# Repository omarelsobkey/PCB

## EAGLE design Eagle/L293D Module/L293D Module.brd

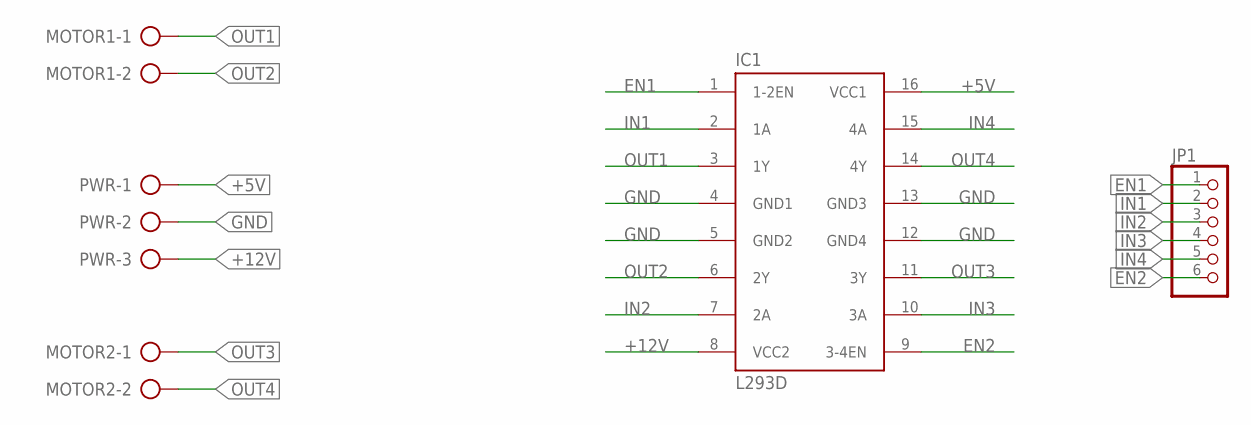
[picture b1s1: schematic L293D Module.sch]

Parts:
IC1: L293D; DIL16
JP1: PINHD-1X6; 1X06
MOTOR1, MOTOR2: AK500/2-H
PWR: AK500/3-H

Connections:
+5V: IC1.16 (VCC1), PWR.1
+12V: IC1.8 (VCC2), PWR.3
EN1: IC1.1 (1-2EN), JP1.1
EN2: IC1.9 (3-4EN), JP1.6
GND: IC1.4 (GND1), IC1.5 (GND2), IC1.12 (GND4), IC1.13 (GND3), PWR.2
IN1: IC1.2 (1A), JP1.2
IN2: IC1.7 (2A), JP1.3
IN3: IC1.10 (3A), JP1.4
IN4: IC1.15 (4A), JP1.5
OUT1: IC1.3 (1Y), MOTOR1.1
OUT2: IC1.6 (2Y), MOTOR1.2
OUT3: IC1.11 (3Y), MOTOR2.1
OUT4: IC1.14 (4Y), MOTOR2.2

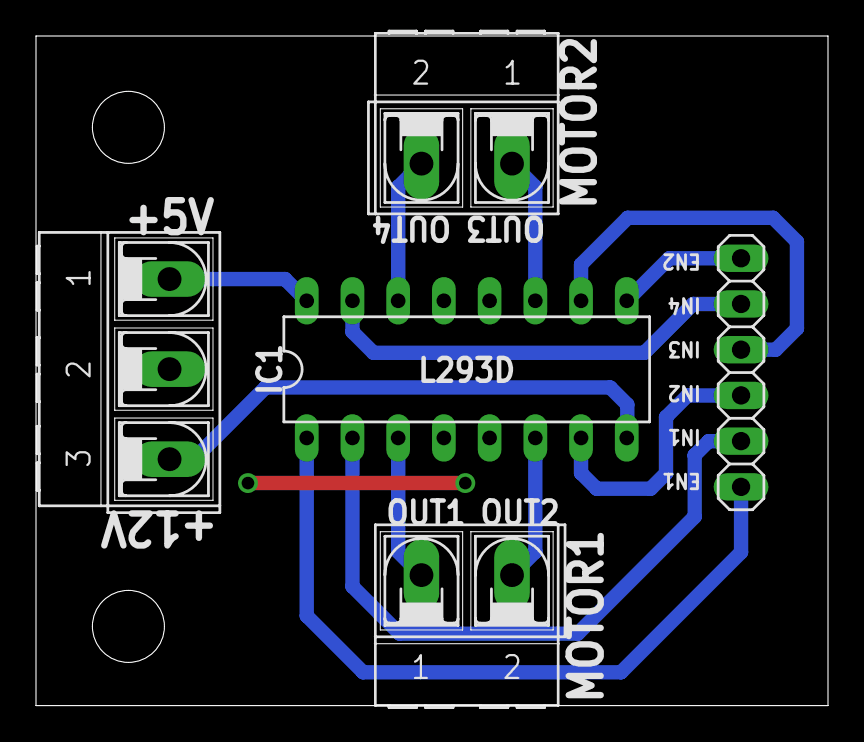
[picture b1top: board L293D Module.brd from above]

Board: 2 copper layers, 44.0 x 37.2 mm, 5 parts (0 on the bottom side), 13 nets.

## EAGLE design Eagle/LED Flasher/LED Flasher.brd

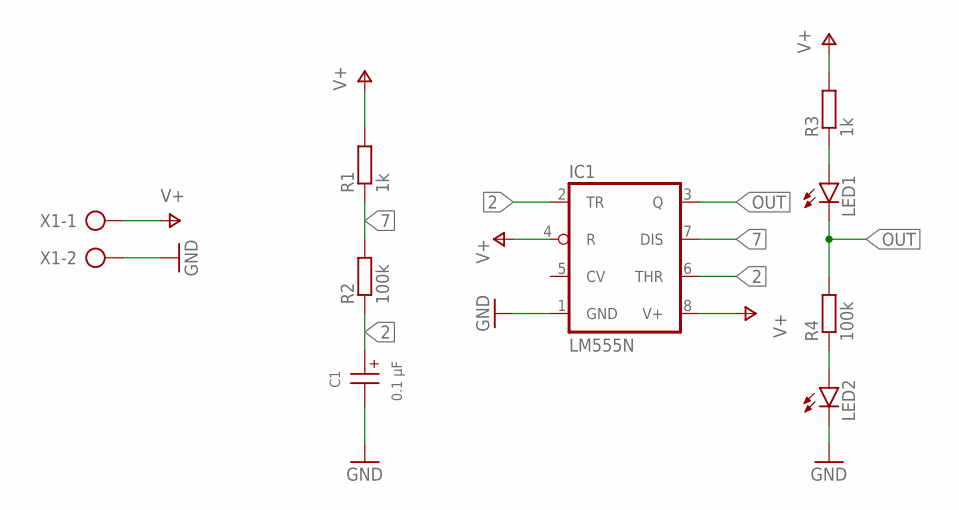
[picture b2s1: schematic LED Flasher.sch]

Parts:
C1: 0.1 µF; WCAP-ATG8_5X11(DXL)
IC1: LM555N; DIL08
LED1, LED2: LED3MM
R1, R3: 1k; 0204/7
R2, R4: 100k; 0204/7
X1: AK300/2

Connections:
2: C1.1 (+), IC1.2 (TR), IC1.6 (THR), R2.1
7: IC1.7 (DIS), R1.1, R2.2
GND: C1.2 (-), IC1.1 (GND), LED2.K (C), X1.2
unnamed: LED1.A, R3.1
unnamed: LED2.A, R4.1
OUT: IC1.3 (Q), LED1.K (C), R4.2
V+: IC1.4 (R), IC1.8 (V+), R1.2, R3.2, X1.1

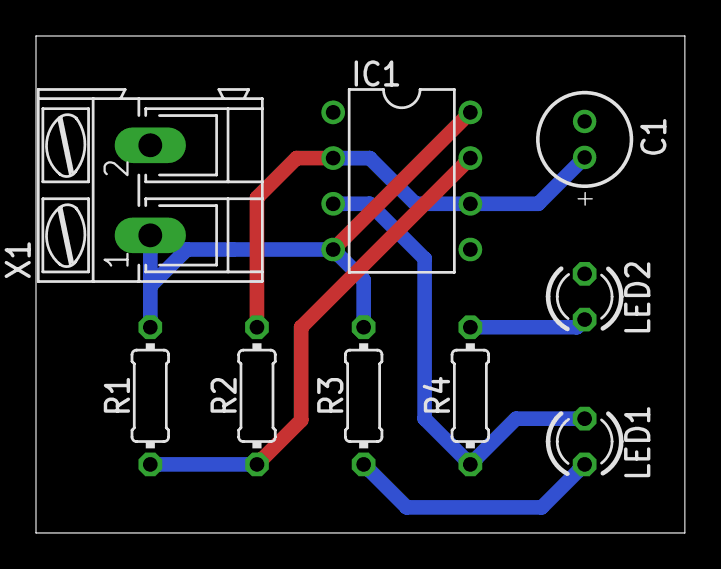
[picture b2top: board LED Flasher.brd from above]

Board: 2 copper layers, 36.0 x 27.6 mm, 9 parts (0 on the bottom side), 7 nets.

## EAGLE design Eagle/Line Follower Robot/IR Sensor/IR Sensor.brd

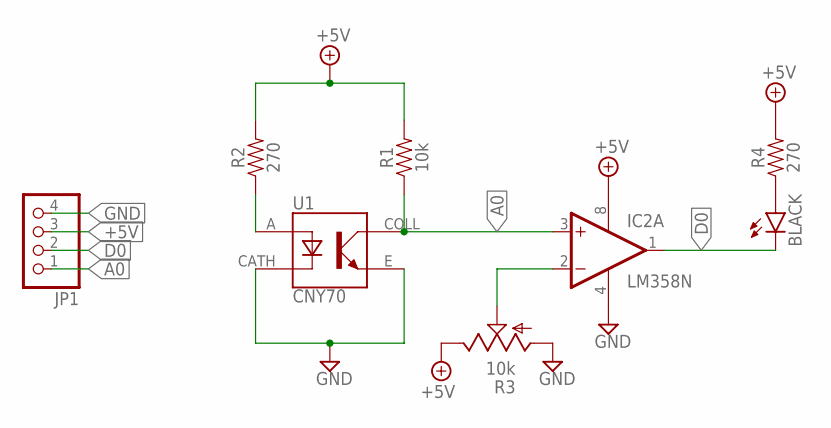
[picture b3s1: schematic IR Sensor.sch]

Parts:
BLACK: LED3MM
IC2: LM358N; DIL08
JP1: PINHD-1X4/90; 1X04/90
R1: 10k; AXIAL-0.3
R2, R4: 270; AXIAL-0.3
R3: 10k; CA6V
U1: CNY70; DIPS254W50P254L710H600Q4

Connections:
+5V: IC2.8 (V+), JP1.3, R1.P$2 (2), R2.P$2 (2), R3.E, R4.P$2 (2)
A0: IC2.3 (+IN), JP1.1, R1.P$1 (1), U1.COLL
D0: BLACK.K (C), IC2.1 (OUT), JP1.2
GND: IC2.4 (V-), JP1.4, R3.A, U1.CATH, U1.E
unnamed: R2.P$1 (1), U1.A
unnamed: IC2.2 (-IN), R3.S
unnamed: BLACK.A, R4.P$1 (1)

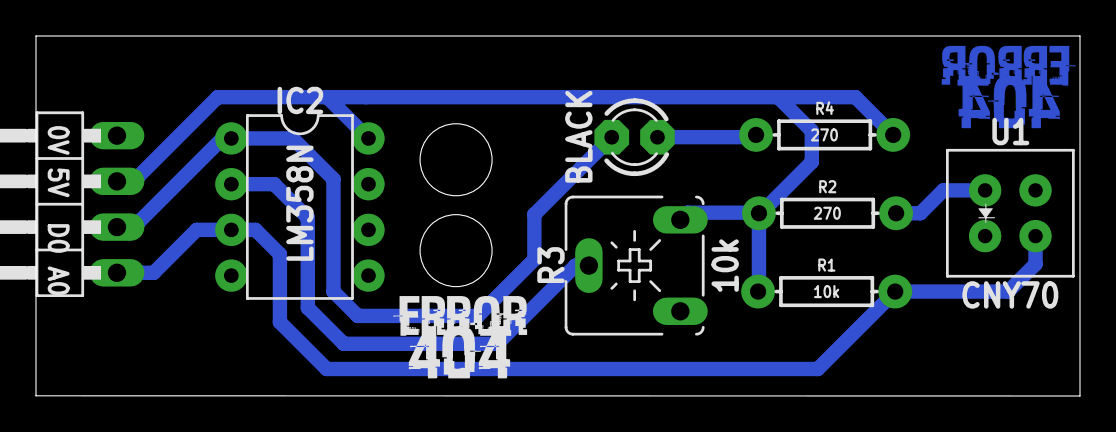
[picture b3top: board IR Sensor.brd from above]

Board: 2 copper layers, 58.0 x 20.0 mm, 10 parts (1 on the bottom side), 7 nets.

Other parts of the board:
U$1: ERROR404_X0.5_T
U$2: ERROR404_X0.5_TN

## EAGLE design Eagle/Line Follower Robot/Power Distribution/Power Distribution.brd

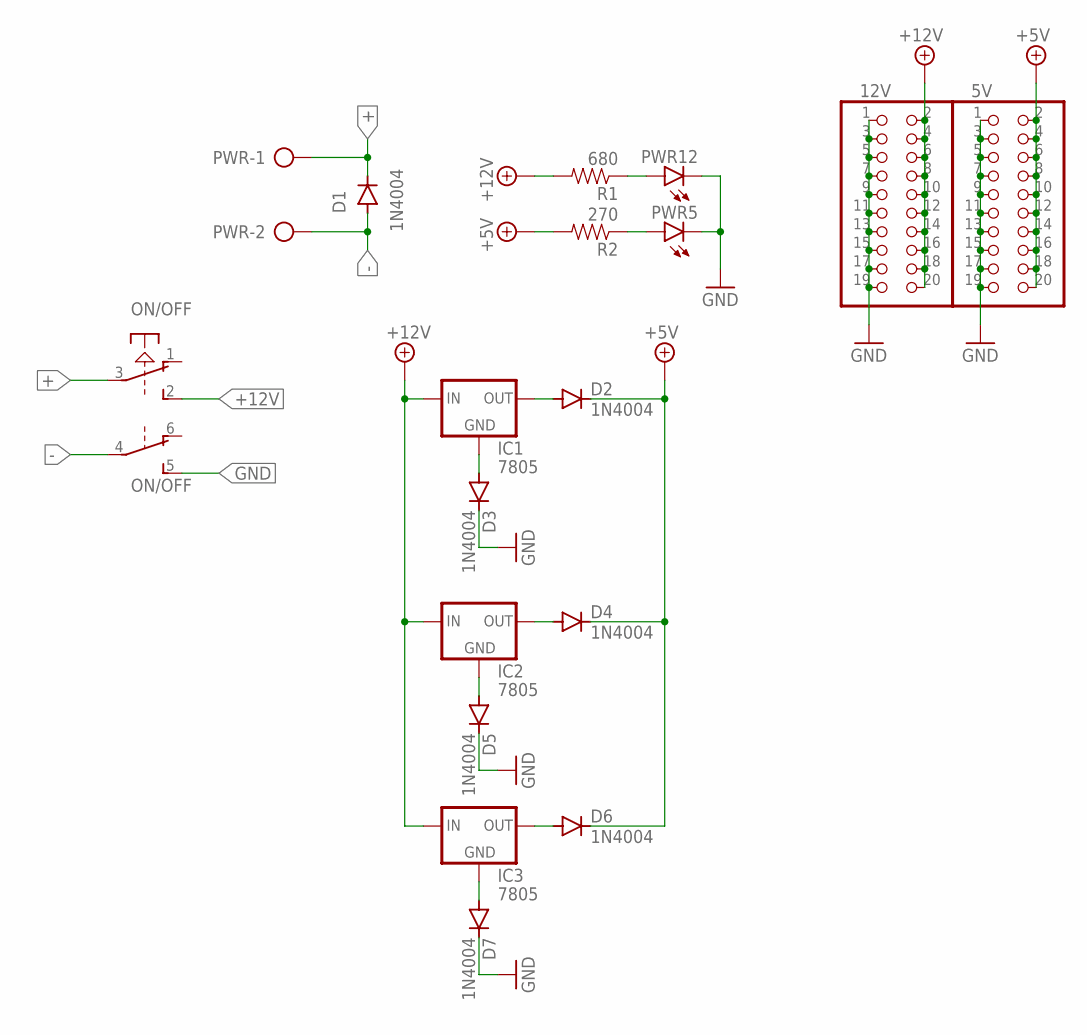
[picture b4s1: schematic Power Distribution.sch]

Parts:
5V, 12V: PINHD-2X10; 2X10
D1, D2, D3, D4, D5, D6, D7: 1N4004; DO41-10
IC1, IC2, IC3: 7805; 78XXS
ON/OFF: PVA2R
PWR: AK500/2-H
PWR5, PWR12: LED3MM
R1: 680; AXIAL-0.3
R2: 270; AXIAL-0.3

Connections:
+: D1.C, ON/OFF.3, PWR.1
+5V: 5V.2, 5V.4, 5V.6, 5V.8, 5V.10, 5V.12, 5V.14, 5V.16, 5V.18, 5V.20, D2.C, D4.C, D6.C, R2.P$2 (2)
+12V: 12V.2, 12V.4, 12V.6, 12V.8, 12V.10, 12V.12, 12V.14, 12V.16, 12V.18, 12V.20, IC1.IN, IC2.IN, IC3.IN, ON/OFF.2 (S), R1.P$2 (2)
-: D1.A, ON/OFF.4, PWR.2
GND: 5V.1, 5V.3, 5V.5, 5V.7, 5V.9, 5V.11, 5V.13, 5V.15, 5V.17, 5V.19, 12V.1, 12V.3, 12V.5, 12V.7, 12V.9, 12V.11, 12V.13, 12V.15, 12V.17, 12V.19, D3.C, D5.C, D7.C, ON/OFF.5 (S), PWR5.K (C), PWR12.K (C)
unnamed: PWR12.A, R1.P$1 (1)
unnamed: D7.A, IC3.GND
unnamed: PWR5.A, R2.P$1 (1)
unnamed: D5.A, IC2.GND
unnamed: D3.A, IC1.GND
unnamed: D2.A, IC1.OUT
unnamed: D6.A, IC3.OUT
unnamed: D4.A, IC2.OUT

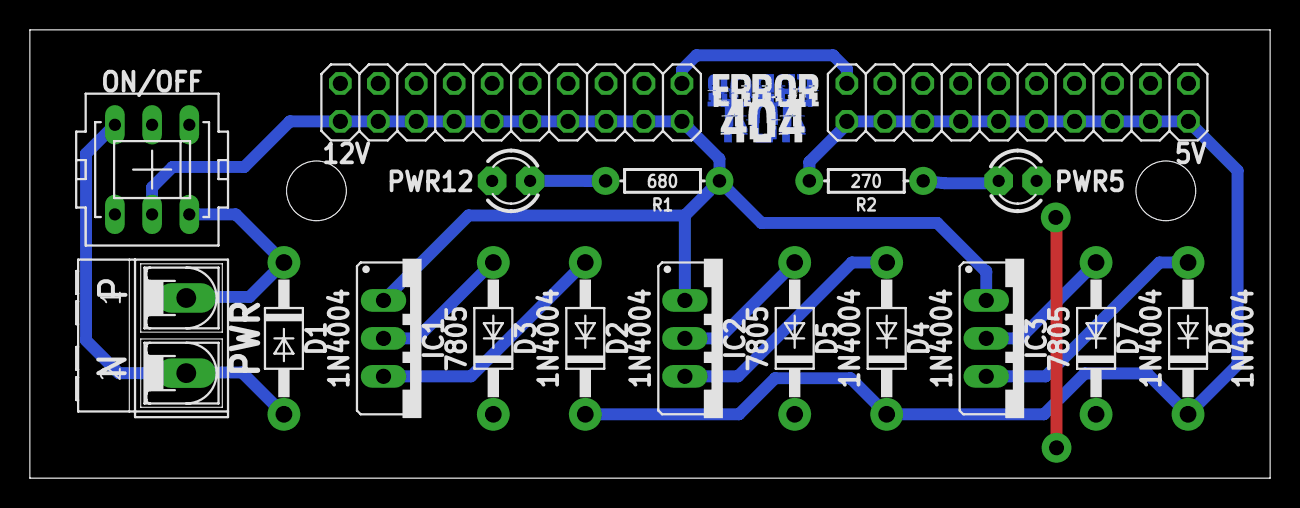
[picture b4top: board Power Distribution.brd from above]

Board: 2 copper layers, 83.0 x 30.0 mm, 20 parts (1 on the bottom side), 13 nets.

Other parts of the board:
U$1: ERROR404_X0.5_T
U$2: ERROR404_X0.5_TN

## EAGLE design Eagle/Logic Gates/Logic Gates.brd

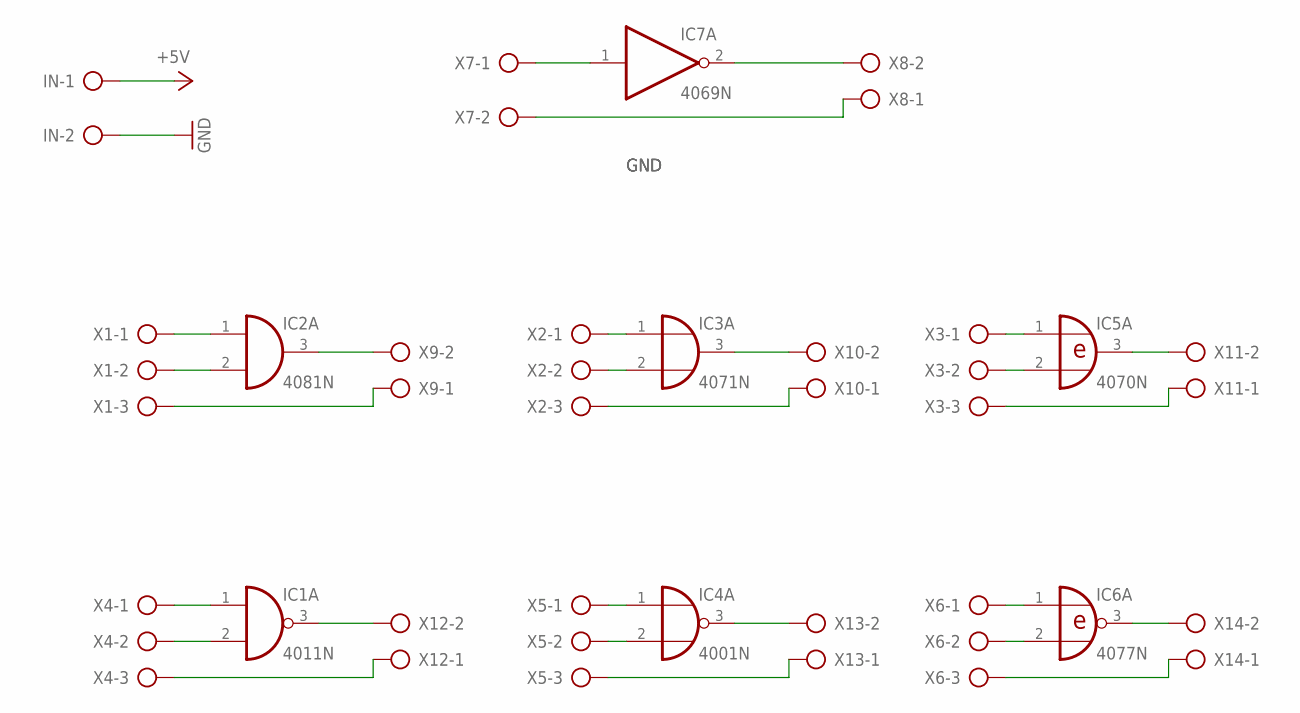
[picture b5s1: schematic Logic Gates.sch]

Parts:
IC1: 4011N; DIL14
IC2: 4081N; DIL14
IC3: 4071N; DIL14
IC4: 4001N; DIL14
IC5: 4070N; DIL14
IC6: 4077N; DIL14
IC7: 4069N; DIL14
IN: AK300/2
X1, X2, X3, X4, X5, X6: AK300/3
X7, X8, X9, X10, X11, X12, X13, X14: AK300/2

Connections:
+5V: IC1.14 (VDD), IC2.14 (VDD), IC3.14 (VDD), IC4.14 (VDD), IC5.14 (VDD), IC6.14 (VDD), IC7.14 (VDD), IN.1
GND: IC1.7 (VSS), IC2.7 (VSS), IC3.7 (VSS), IC4.7 (VSS), IC5.7 (VSS), IC6.7 (VSS), IC7.7 (VSS), IN.2, X1.3, X2.3, X3.3, X4.3, X5.3, X6.3, X7.2, X8.1, X9.1, X10.1, X11.1, X12.1, X13.1, X14.1
unnamed: IC7.1 (I), X7.1
unnamed: IC7.2 (O), X8.2
unnamed: IC2.1 (I0), X1.1
unnamed: IC2.3 (O), X9.2
unnamed: IC2.2 (I1), X1.2
unnamed: IC3.3 (O), X10.2
unnamed: IC5.3 (O), X11.2
unnamed: IC3.1 (I0), X2.1
unnamed: IC3.2 (I1), X2.2
unnamed: IC6.3 (O), X14.2
unnamed: IC4.3 (O), X13.2
unnamed: IC5.1 (I0), X3.1
unnamed: IC1.3 (O), X12.2
unnamed: IC5.2 (I1), X3.2
unnamed: IC1.1 (I0), X4.1
unnamed: IC1.2 (I1), X4.2
unnamed: IC4.1 (I0), X5.1
unnamed: IC4.2 (I1), X5.2
unnamed: IC6.1 (I0), X6.1
unnamed: IC6.2 (I1), X6.2

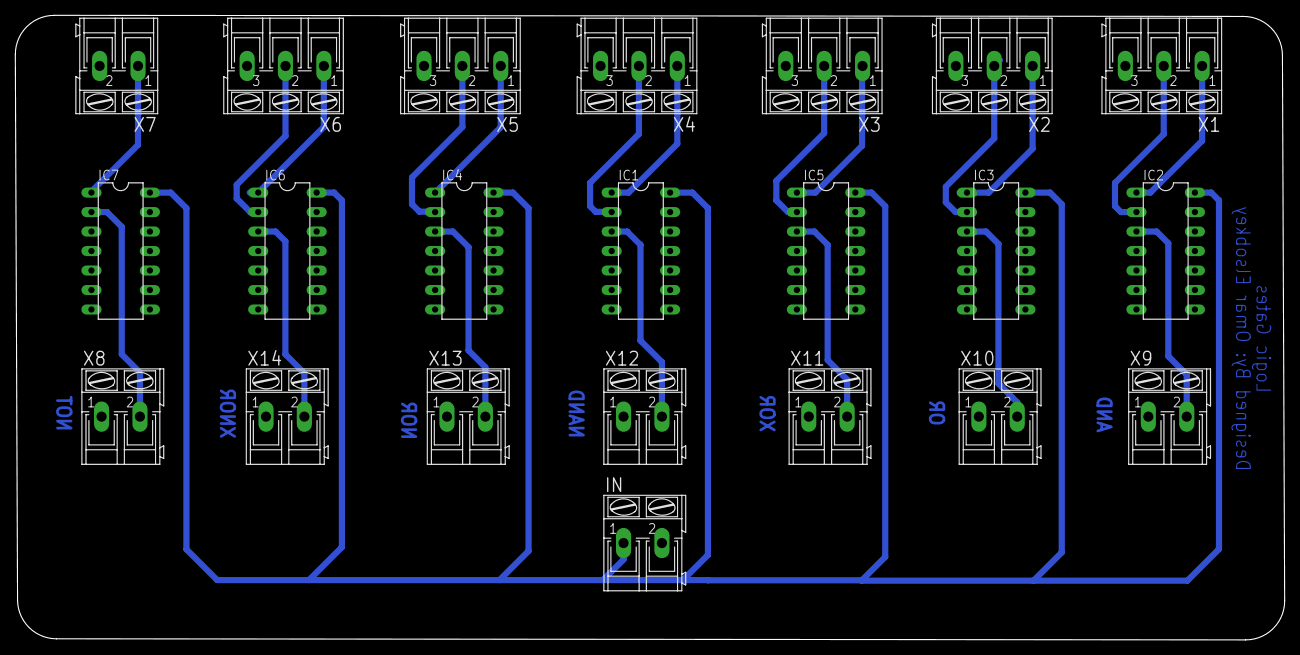
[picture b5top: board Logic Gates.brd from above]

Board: 2 copper layers, 165.5 x 81.4 mm, 22 parts (0 on the bottom side), 22 nets.

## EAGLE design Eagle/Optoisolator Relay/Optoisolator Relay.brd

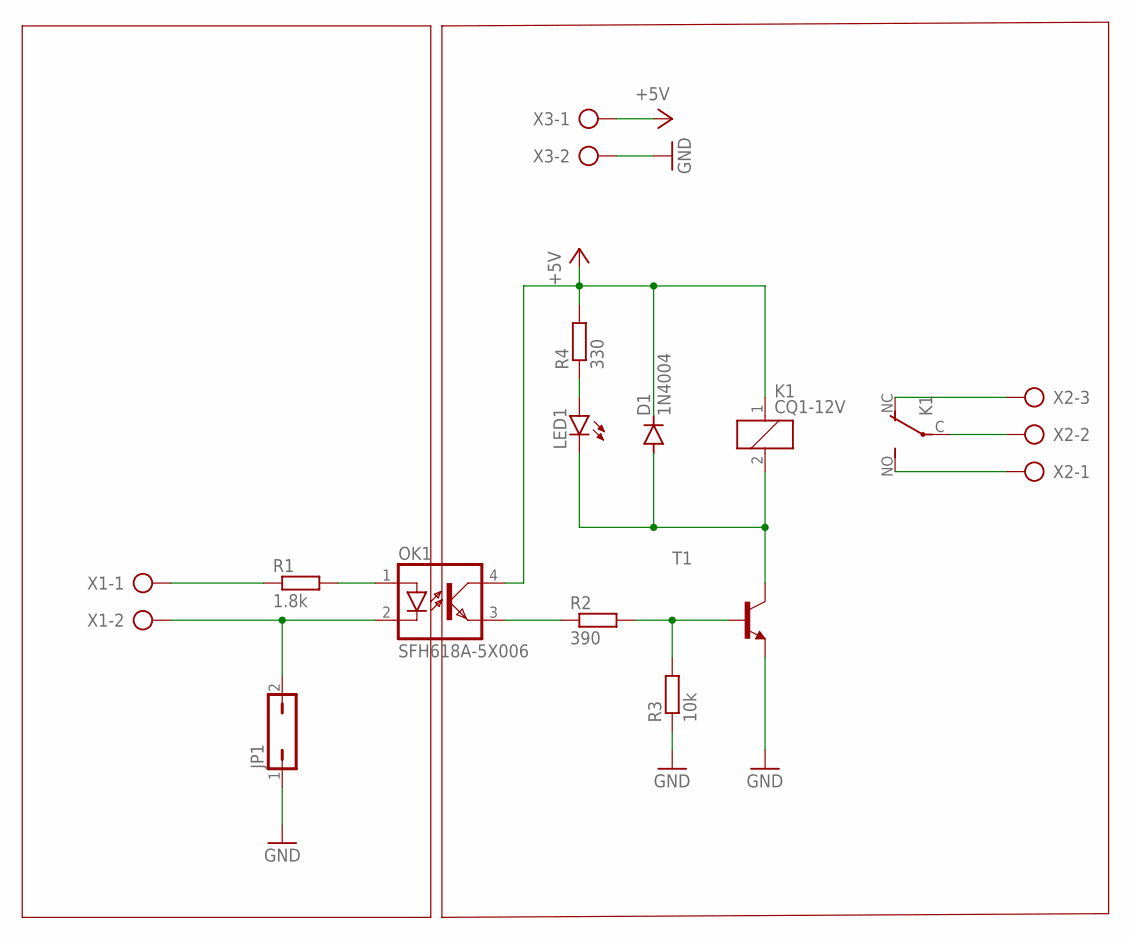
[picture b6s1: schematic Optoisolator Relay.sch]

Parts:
D1: 1N4004; DO41-10
JP1: JP1Q; JP1
K1: CQ1-12V; CQ1
LED1: LED3MM
OK1: SFH618A-5X006; DIP4-400
R1: 1.8k; 0204/7
R2: 390; 0204/7
R3: 10k; 0204/7
R4: 330; 0204/7
T1: 2N2222-NPN-TO92-EBC; TO92-EBC
X1, X3: AK300/2
X2: AK300/3

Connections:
+5V: D1.C, K1.1, OK1.4 (COL), R4.2, X3.1
GND: JP1.1, R3.1, T1.E, X3.2
unnamed: R1.1, X1.1
unnamed: OK1.1 (A), R1.2
unnamed: D1.A, K1.2, LED1.K (C), T1.C
unnamed: OK1.3 (EMIT), R2.1
unnamed: R2.2, R3.2, T1.B
unnamed: LED1.A, R4.1
unnamed: K1.C, X2.2
unnamed: K1.NO (S), X2.1
unnamed: K1.NC (O), X2.3
unnamed: JP1.2, OK1.2 (C), X1.2

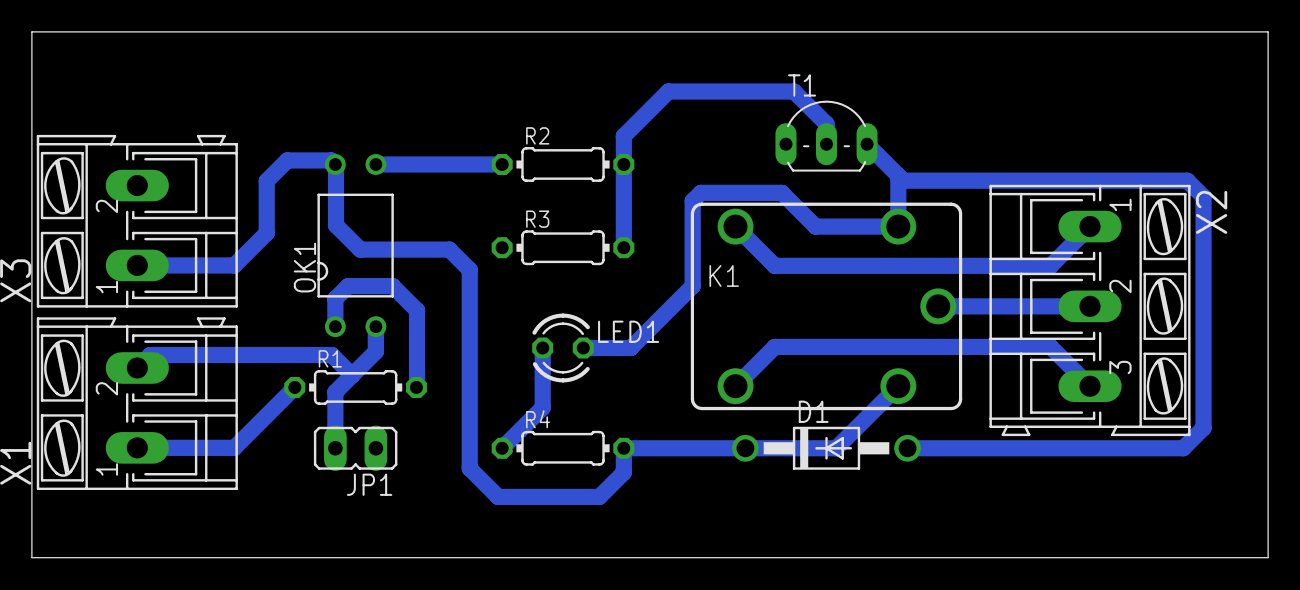
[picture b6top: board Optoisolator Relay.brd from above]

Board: 2 copper layers, 77.5 x 32.9 mm, 13 parts (0 on the bottom side), 12 nets.

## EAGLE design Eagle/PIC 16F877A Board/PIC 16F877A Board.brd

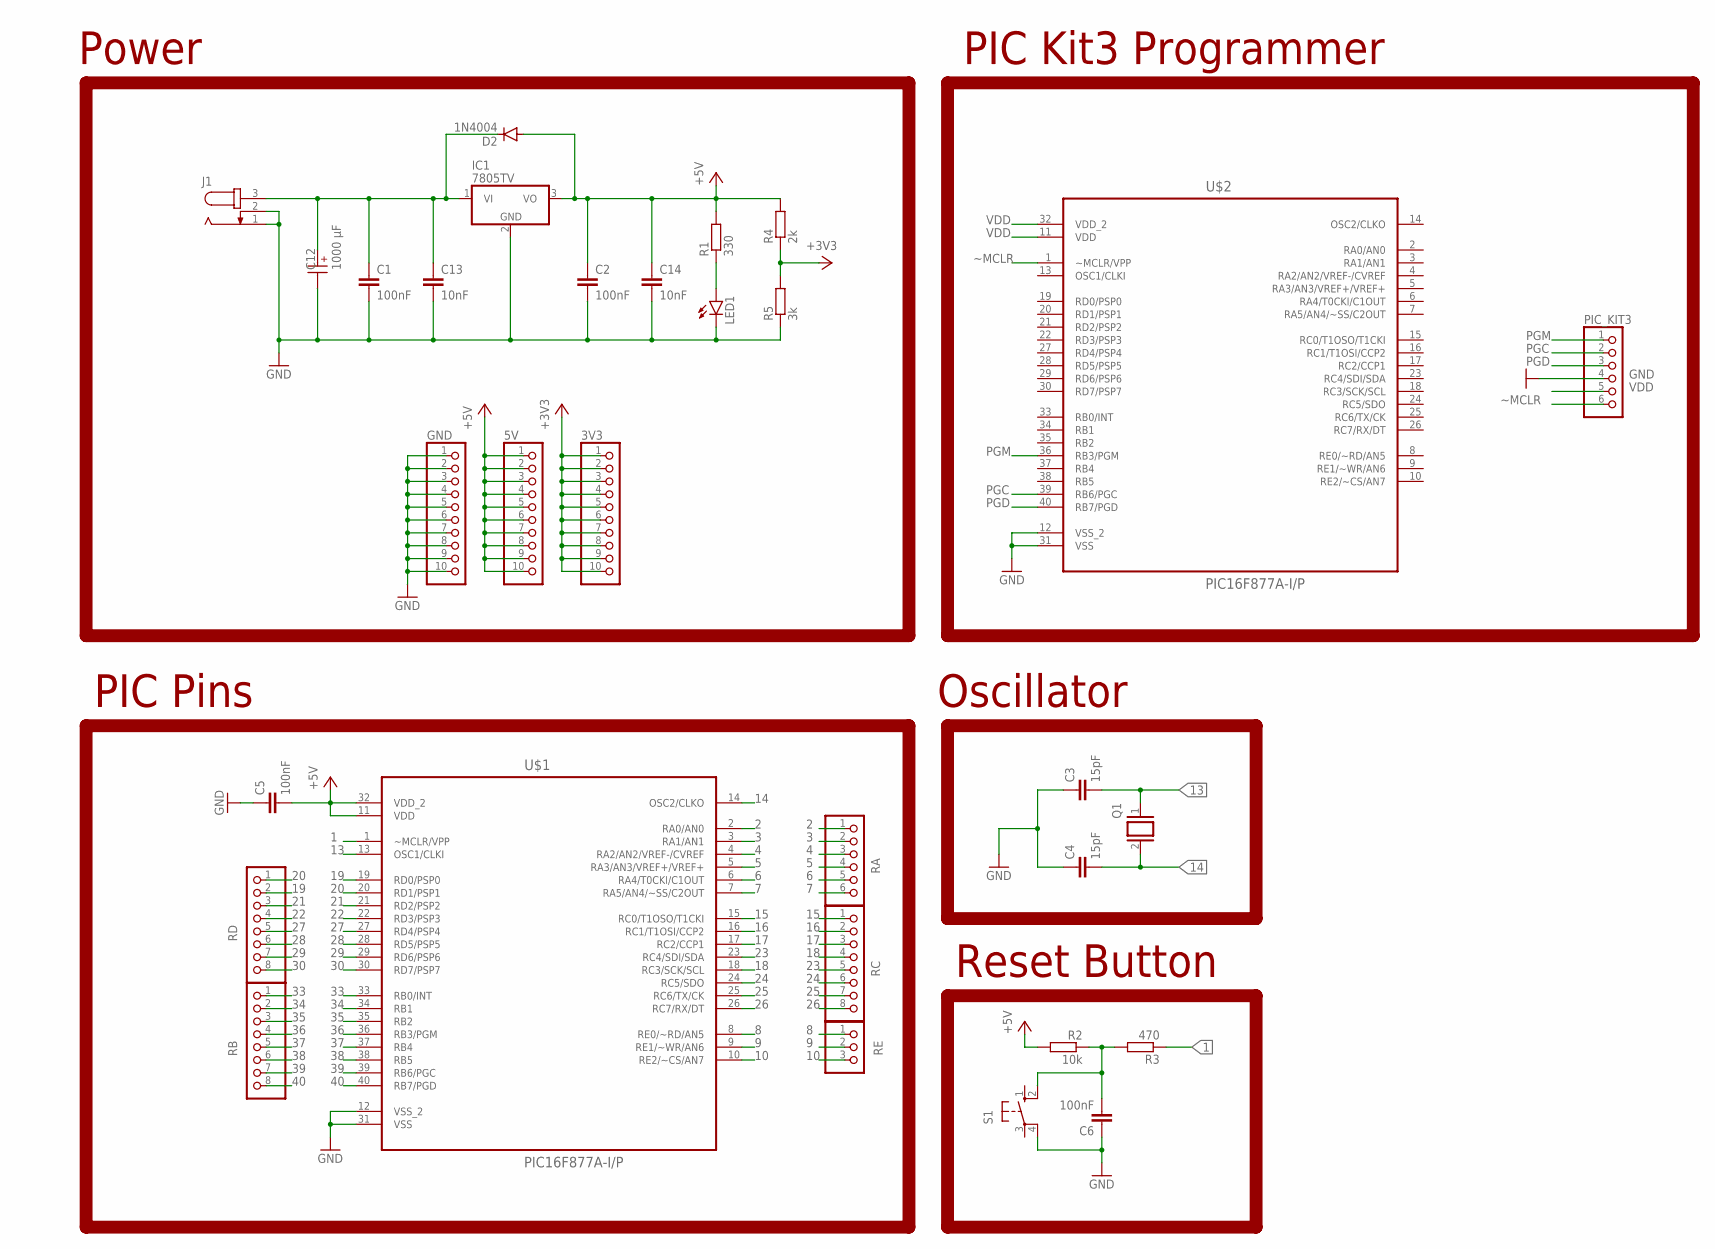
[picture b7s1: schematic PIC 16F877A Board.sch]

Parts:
3V3, 5V: PINHD-1X10; 1X10
C1, C2, C5, C6: 100nF; C025-025X050
C3, C4: 15pF; C025-025X050
C12: 1000 µF; WCAP-ATG8_10X12.5(DXL)
C13, C14: 10nF; C025-025X050
D2: 1N4004; DO41-10
GND: PINHD-1X10; 1X10
IC1: 7805TV; TO220V
J1: JACK-PLUG0; SPC4077
LED1: LED3MM
PIC_KIT3: PINHD-1X6; 1X06
Q1: XTAL/S; QS
R1: 330; 0204/7
R2: 10k; 0204/7
R3: 470; 0204/7
R4: 2k; 0204/7
R5: 3k; 0204/7
RA: PINHD-1X6; 1X06
RB: PINHD-1X8; 1X08
RC: PINHD-1X8; 1X08
RD: PINHD-1X8; 1X08
RE: PINHD-1X3; 1X03
S1: 10-XX; B3F-10XX
U$1, U$2: PIC16F877A-I/P; 16F877A

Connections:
1: R3.1, U$1.1 (~MCLR/VPP)
2: RA.1, U$1.2 (RA0/AN0)
3: RA.2, U$1.3 (RA1/AN1)
4: RA.3, U$1.4 (RA2/AN2/VREF-/CVREF)
5: RA.4, U$1.5 (RA3/AN3/VREF+/VREF+)
6: RA.5, U$1.6 (RA4/T0CKI/C1OUT)
7: RA.6, U$1.7 (RA5/AN4/~SS/C2OUT)
8: RE.1, U$1.8 (RE0/~RD/AN5)
9: RE.2, U$1.9 (RE1/~WR/AN6)
10: RE.3, U$1.10 (RE2/~CS/AN7)
13: C3.2, Q1.1, U$1.13 (OSC1/CLKI)
14: C4.2, Q1.2, U$1.14 (OSC2/CLKO)
15: RC.1, U$1.15 (RC0/T1OSO/T1CKI)
16: RC.2, U$1.16 (RC1/T1OSI/CCP2)
17: RC.3, U$1.17 (RC2/CCP1)
18: RC.4, U$1.18 (RC3/SCK/SCL)
19: RD.2, U$1.19 (RD0/PSP0)
20: RD.1, U$1.20 (RD1/PSP1)
21: RD.3, U$1.21 (RD2/PSP2)
22: RD.4, U$1.22 (RD3/PSP3)
23: RC.5, U$1.23 (RC4/SDI/SDA)
24: RC.6, U$1.24 (RC5/SDO)
25: RC.7, U$1.25 (RC6/TX/CK)
26: RC.8, U$1.26 (RC7/RX/DT)
27: RD.5, U$1.27 (RD4/PSP4)
28: RD.6, U$1.28 (RD5/PSP5)
29: RD.7, U$1.29 (RD6/PSP6)
30: RD.8, U$1.30 (RD7/PSP7)
33: RB.1, U$1.33 (RB0/INT)
34: RB.2, U$1.34 (RB1)
35: RB.3, U$1.35 (RB2)
36: RB.4, U$1.36 (RB3/PGM)
37: RB.5, U$1.37 (RB4)
38: RB.6, U$1.38 (RB5)
39: RB.7, U$1.39 (RB6/PGC)
40: RB.8, U$1.40 (RB7/PGD)
+3V3: 3V3.1, 3V3.2, 3V3.3, 3V3.4, 3V3.5, 3V3.6, 3V3.7, 3V3.8, 3V3.9, 3V3.10, R4.1, R5.2
+5V: 5V.1, 5V.2, 5V.3, 5V.4, 5V.5, 5V.6, 5V.7, 5V.8, 5V.9, 5V.10, C2.1, C5.2, C14.1, D2.A, IC1.3 (VO), R1.2, R2.2, R4.2, U$1.11 (VDD), U$1.32 (VDD_2)
GND: C1.2, C2.2, C3.1, C4.1, C5.1, C6.1, C12.2 (-), C13.2, C14.2, GND.1, GND.2, GND.3, GND.4, GND.5, GND.6, GND.7, GND.8, GND.9, GND.10, IC1.2 (GND), J1.1, J1.2, LED1.K (C), PIC_KIT3.4, R5.1, S1.4 (P1), U$1.12 (VSS_2), U$1.31 (VSS), U$2.12 (VSS_2), U$2.31 (VSS)
unnamed: C1.1, C12.1 (+), C13.1, D2.C, IC1.1 (VI), J1.3
unnamed: C6.2, R2.1, R3.2, S1.2 (S1)
unnamed: LED1.A, R1.1
PGC: PIC_KIT3.2, U$2.39 (RB6/PGC)
PGD: PIC_KIT3.3, U$2.40 (RB7/PGD)
PGM: PIC_KIT3.1, U$2.36 (RB3/PGM)
VDD: PIC_KIT3.5, U$2.11 (VDD), U$2.32 (VDD_2)
~MCLR: PIC_KIT3.6, U$2.1 (~MCLR/VPP)

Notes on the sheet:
PIC Kit3 Programmer
PIC Pins
Oscillator
Reset Button
Power

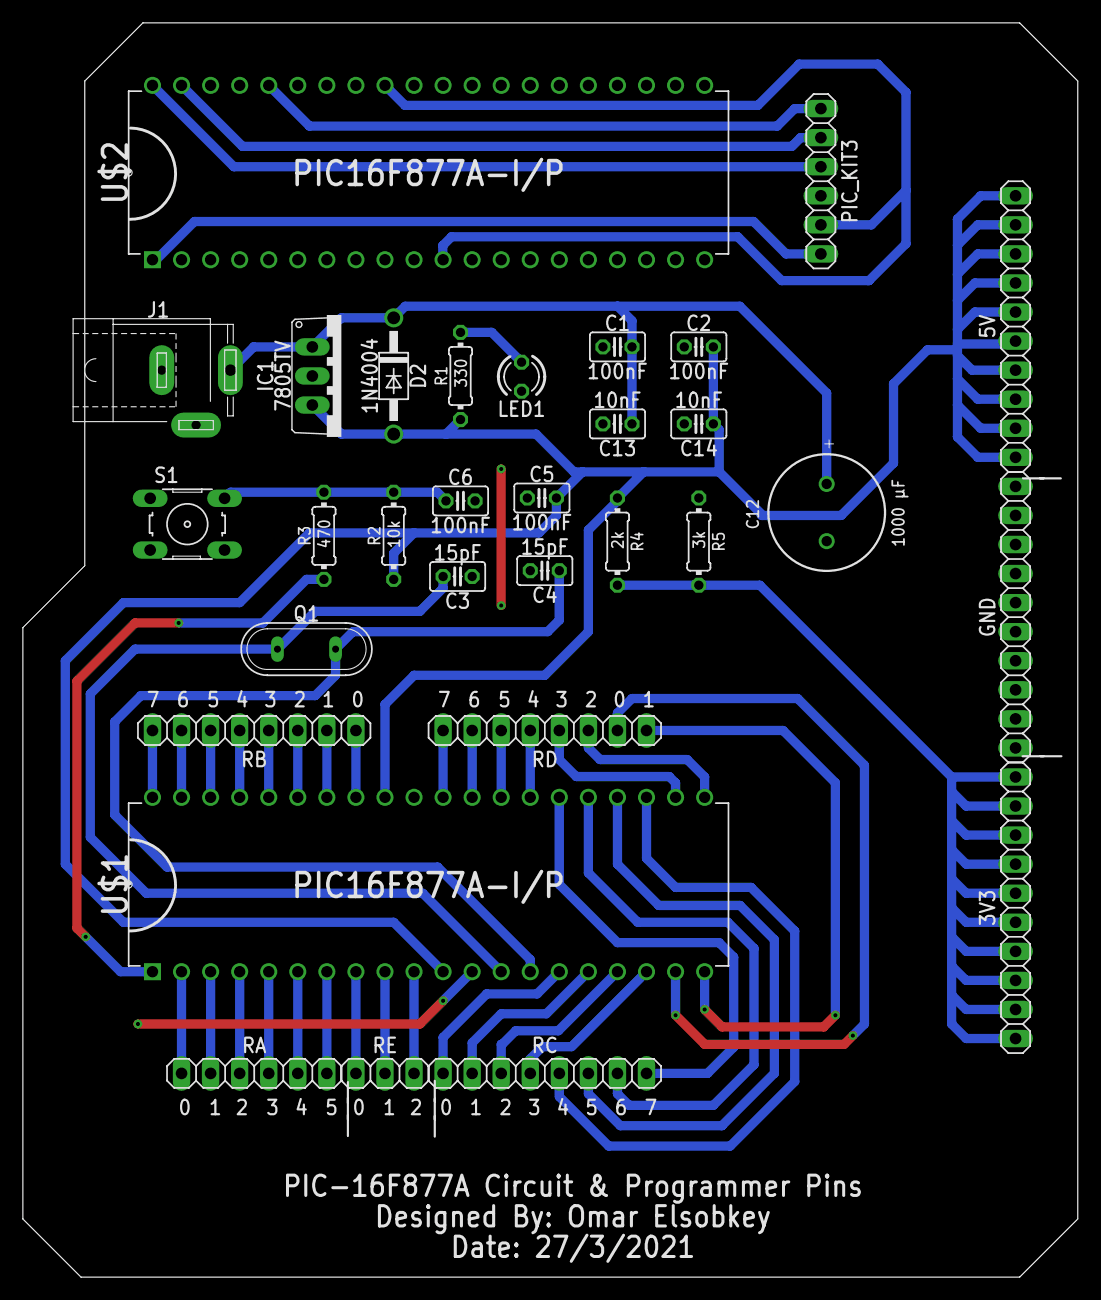
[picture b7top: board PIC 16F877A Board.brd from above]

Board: 2 copper layers, 92.2 x 109.6 mm, 31 parts (0 on the bottom side), 47 nets.

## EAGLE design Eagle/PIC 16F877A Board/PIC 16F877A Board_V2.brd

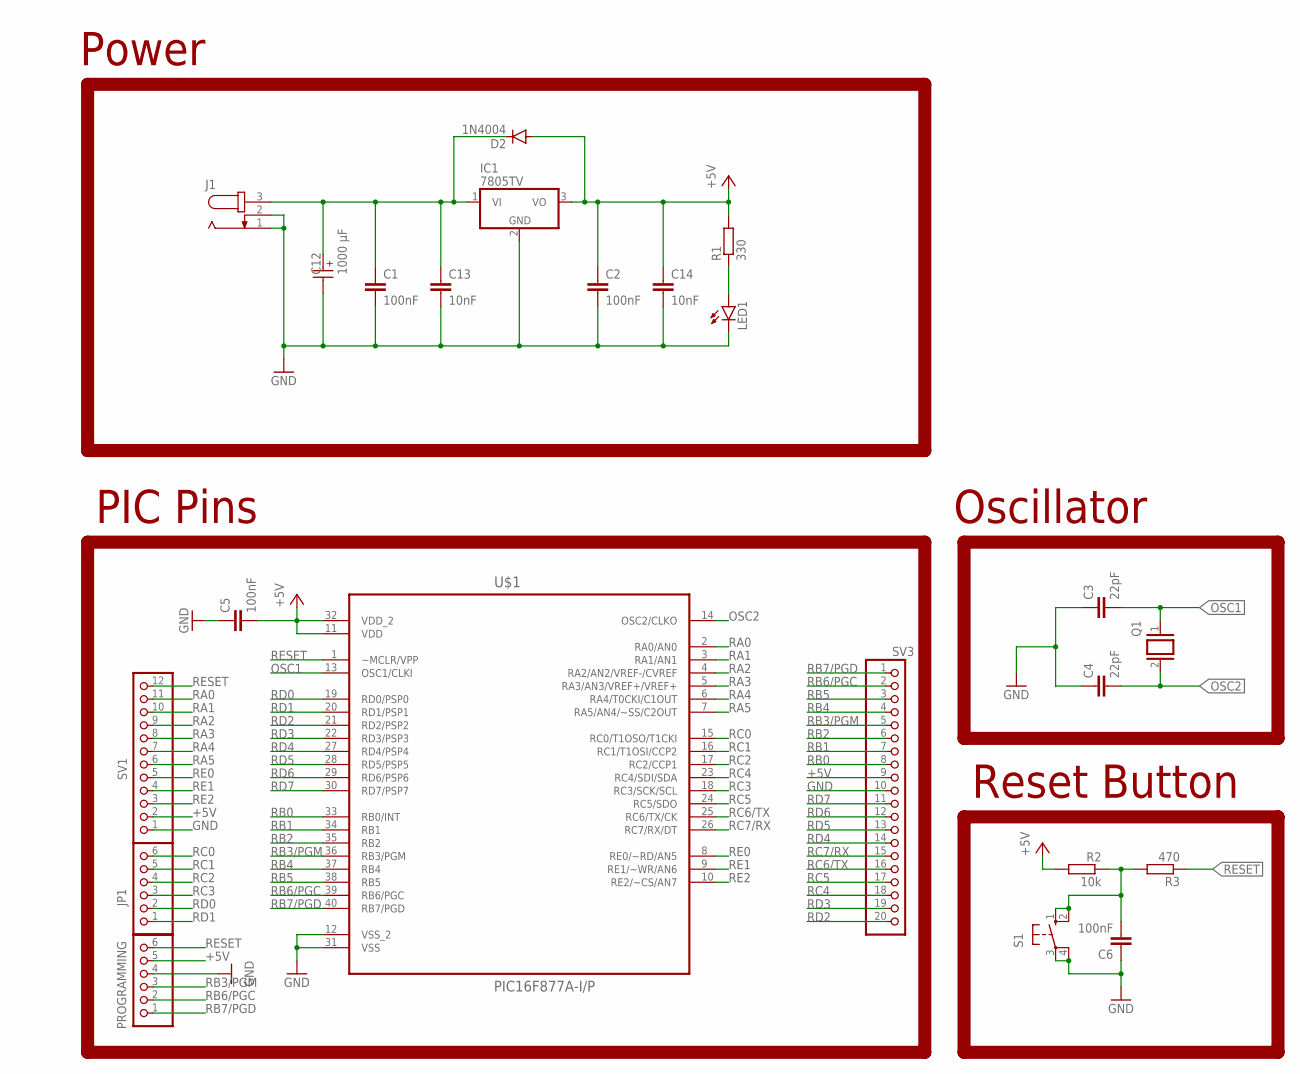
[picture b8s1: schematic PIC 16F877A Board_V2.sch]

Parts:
C1, C2, C5, C6: 100nF; C025-025X050
C3, C4: 22pF; C025-025X050
C12: 1000 µF; WCAP-ATG8_10X12.5(DXL)
C13, C14: 10nF; C025-025X050
D2: 1N4004; DO41-10
IC1: 7805TV; TO220V
J1: JACK-PLUG0; SPC4077
JP1: PINHD-1X6; 1X06
LED1: LED3MM
PROGRAMMING: PINHD-1X6; 1X06
Q1: XTAL/S; QS
R1: 330; 0204/7
R2: 10k; 0204/7
R3: 470; 0204/7
S1: 10-XX; B3F-10XX
SV1: PINHD-1X12; 1X12
SV3: PINHD-1X20; 1X20
U$1: PIC16F877A-I/P; 16F877A

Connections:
+5V: C2.1, C5.2, C14.1, D2.A, IC1.3 (VO), PROGRAMMING.5, R1.2, R2.2, SV1.2, SV3.9, U$1.11 (VDD), U$1.32 (VDD_2)
GND: C1.2, C2.2, C3.1, C4.1, C5.1, C6.1, C12.2 (-), C13.2, C14.2, IC1.2 (GND), J1.1, J1.2, LED1.K (C), PROGRAMMING.4, S1.3, S1.4 (P1), SV1.1, SV3.10, U$1.12 (VSS_2), U$1.31 (VSS)
unnamed: C1.1, C12.1 (+), C13.1, D2.C, IC1.1 (VI), J1.3
unnamed: C6.2, R2.1, R3.2, S1.1 (S), S1.2 (S1)
unnamed: LED1.A, R1.1
OSC1: C3.2, Q1.1, U$1.13 (OSC1/CLKI)
OSC2: C4.2, Q1.2, U$1.14 (OSC2/CLKO)
RA0: SV1.11, U$1.2 (RA0/AN0)
RA1: SV1.10, U$1.3 (RA1/AN1)
RA2: SV1.9, U$1.4 (RA2/AN2/VREF-/CVREF)
RA3: SV1.8, U$1.5 (RA3/AN3/VREF+/VREF+)
RA4: SV1.7, U$1.6 (RA4/T0CKI/C1OUT)
RA5: SV1.6, U$1.7 (RA5/AN4/~SS/C2OUT)
RB0: SV3.8, U$1.33 (RB0/INT)
RB1: SV3.7, U$1.34 (RB1)
RB2: SV3.6, U$1.35 (RB2)
RB3/PGM: PROGRAMMING.3, SV3.5, U$1.36 (RB3/PGM)
RB4: SV3.4, U$1.37 (RB4)
RB5: SV3.3, U$1.38 (RB5)
RB6/PGC: PROGRAMMING.2, SV3.2, U$1.39 (RB6/PGC)
RB7/PGD: PROGRAMMING.1, SV3.1, U$1.40 (RB7/PGD)
RC0: JP1.6, U$1.15 (RC0/T1OSO/T1CKI)
RC1: JP1.5, U$1.16 (RC1/T1OSI/CCP2)
RC2: JP1.4, U$1.17 (RC2/CCP1)
RC3: JP1.3, U$1.18 (RC3/SCK/SCL)
RC4: SV3.18, U$1.23 (RC4/SDI/SDA)
RC5: SV3.17, U$1.24 (RC5/SDO)
RC6/TX: SV3.16, U$1.25 (RC6/TX/CK)
RC7/RX: SV3.15, U$1.26 (RC7/RX/DT)
RD0: JP1.2, U$1.19 (RD0/PSP0)
RD1: JP1.1, U$1.20 (RD1/PSP1)
RD2: SV3.20, U$1.21 (RD2/PSP2)
RD3: SV3.19, U$1.22 (RD3/PSP3)
RD4: SV3.14, U$1.27 (RD4/PSP4)
RD5: SV3.13, U$1.28 (RD5/PSP5)
RD6: SV3.12, U$1.29 (RD6/PSP6)
RD7: SV3.11, U$1.30 (RD7/PSP7)
RE0: SV1.5, U$1.8 (RE0/~RD/AN5)
RE1: SV1.4, U$1.9 (RE1/~WR/AN6)
RE2: SV1.3, U$1.10 (RE2/~CS/AN7)
RESET: PROGRAMMING.6, R3.1, SV1.12, U$1.1 (~MCLR/VPP)

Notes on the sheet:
PIC Pins
Oscillator
Reset Button
Power

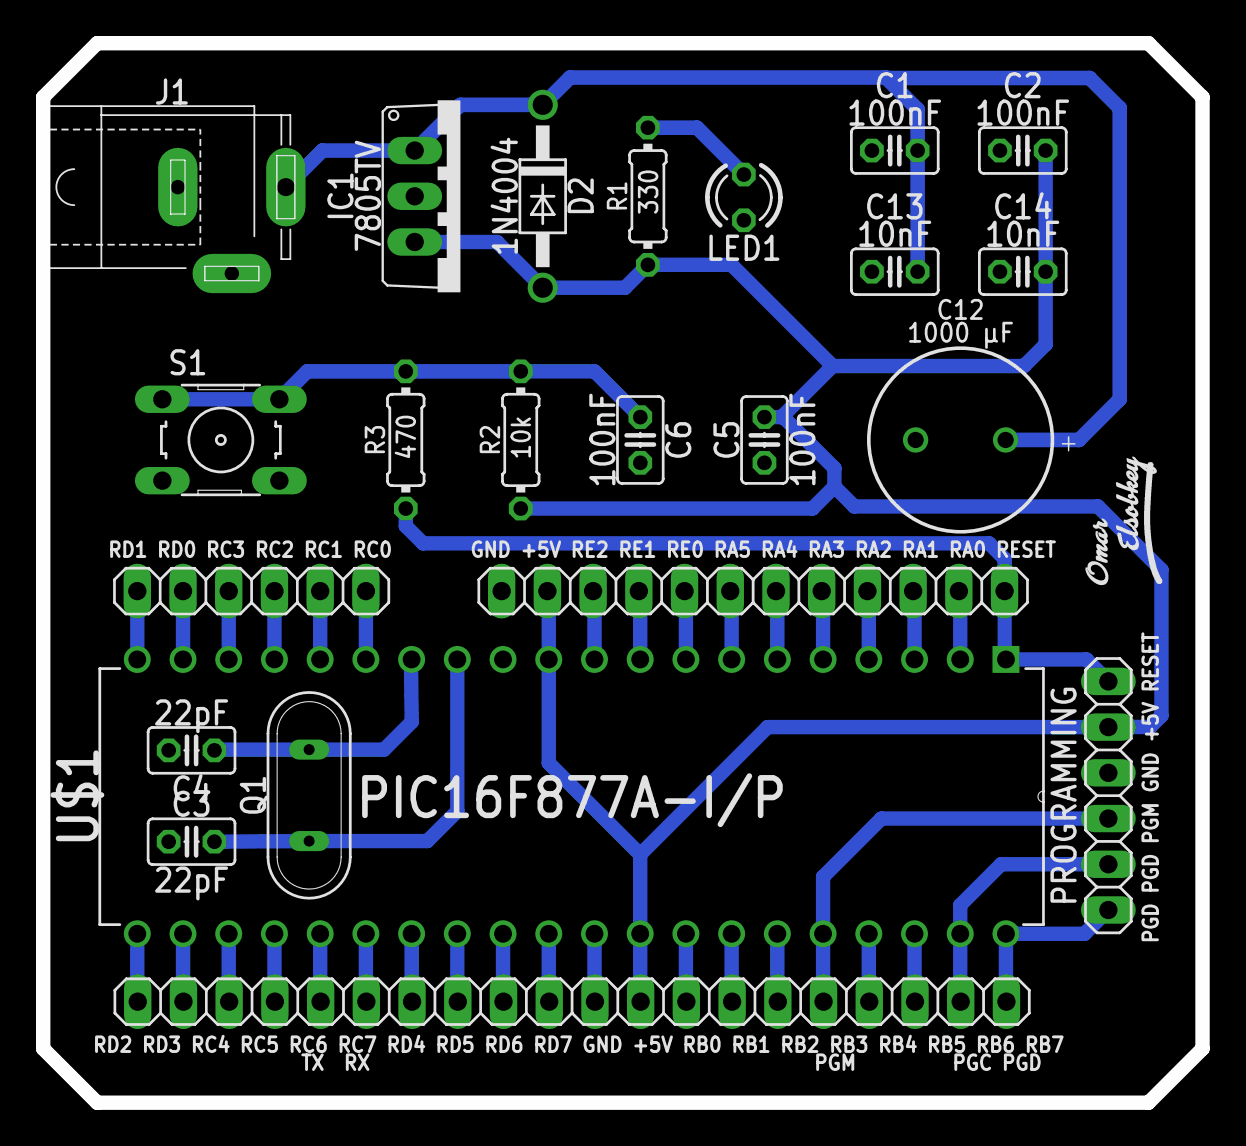
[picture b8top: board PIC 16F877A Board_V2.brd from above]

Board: 2 copper layers, 64.4 x 58.9 mm, 25 parts (1 on the bottom side), 41 nets.

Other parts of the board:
U$2, U$4: OMAR_ELSOBKEY_X0.5_TN

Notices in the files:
parts and their libraries:
Aluminium Electrolyt Capacitors: Copyright: Würth Elektronik
SparkFun-Resistors: Licensing: Creative Commons ShareAlike 4.0 International - https://creativecommons.org/licenses/by-sa/4.0
